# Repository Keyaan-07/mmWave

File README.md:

# mmWave Radar
This project includes building a complete mmWave radar that could operate at 60GHz. It uses the Texas Instruments IWRL6432 as the radar IC. This radar IC is operable between 57GHz-64GHz. The main goal of this project is to make a small module to use this IC as a radar. 
The board is a 6 layer board(4 layer was possible but 6 layers was cheaper). The 6 layer board costs only $2. 

[KICANVAS](https://kicanvas.org?)

# Images
Schematic:  
  
PCB:  

3d: 

# BOM
because the top sides contains BGA footprint which i've never soldered before, i am doing PCBA services for the top side and i will assemble the bottom side by myself
| ITEM                        | COST  | NOTE                           |
| --------------------------- | ----- | ------------------------------ |
| PCB                         | 2     | 6-Layer PCB                    |
| PCBA                        | 51.71 | PCBA service from jlcpcb.com   |
| SHIPPING from JLC           | 9.28  | shipping cost                  |
| PCBA discount               | -15    | 15 USD coupon from JLCONE yayy(valid till 19 sept) |
| LCSC Total (BOM_PCB_Bottom) | 14.55 | bottom side all parts          |
| Total                       | 62.54 | USD                            |

----
### BOM - Top Side of PCB(PCBA recommened)
| Designator                          | Designation      | Footprint                              | Price   | Quantity(for 2 PCBA) | Amount(USD) | JLCPCB Part Number |
| ----------------------------------- | ---------------- | -------------------------------------- | ------- | -------------------- | ----------- | ------------------ |
| C1, C2                              | 15p              | 402                                    | 0.001   | 4                    | 0.004       | C1548              |
| C6, C8, C10, C12, C14               | 2u2              | 603                                    | 0.006   | 10                   | 0.06        | C23630             |
| C5, C11, C13, C18, C19, C25, C7, C9 | 10u              | 603                                    | 0.056   | 16                   | 0.896       | C19702             |
| R2, R3                              | 100k             | 402                                    | 0.001   | 2                    | 0.002       | C25741             |
| R4, R5, R6                          | 10k              | 402                                    | 0.001   | 3                    | 0.003       | C25744             |
| U1                                  | IWRL6432BDBAAMFR | BGA-102_L6.5-W6.5-P0.50-TL_TI_IWRL6432 | 16.0095 | 2                    | 32.019      | C22428198          |
| U2                                  | W25Q128JVS       | SOIC-8_5.3x5.3mm_P1.27mm               | 1.131   | 2                    | 2.262       | C97521             |
| U3                                  | AMS1117-3.3      | SOT-223-3_TabPin2                      | 0.1615  | 2                    | 0.323       | C6186              |
|                                     |                  |                                        |         | Total                | 35.569      |                    |
| PCB Cost                            | 2                | USD                                    |         |                      |             |                    |
| Economic PCBA price                 | 51.71            | USD                                    |         |                      |             |                    |
| Total                               | 53.71            | USD                                    |         |                      |             |                    |

----
### BOM - bottom side of PCB(order and solder yourself)
if DNO is yes, i am not ordering the respective parts and cost has not been added to BOM.
| Designator             | Designation        | Footprint                          | DNO - Do not order | MOQ | Price  | Quantity | Amount(USD) | Supplier link                                      |
| ---------------------- | ------------------ | ---------------------------------- | ------------------ | --- | ------ | -------- | ----------- | -------------------------------------------------- |
| C3, C20, C22, C23, C24 | 10u                | 603                                | No                 | Yes | 0.0197 | 20       | 0.394       | https://www.lcsc.com/product-detail/C7393892.html  |
| C4, C21                | 2u2                | 603                                | No                 | Yes | 0.0228 | 20       | 0.456       | https://www.lcsc.com/product-detail/C48579298.html |
| C15                    | 47n                | 402                                | Yes                | \-  | 0      | 1        | 0           | https://www.lcsc.com/product-detail/C5142571.html  |
| C16, C17               | 1u                 | 603                                | No                 | Yes | 0.0056 | 50       | 0.28        | https://www.lcsc.com/product-detail/C29936.html    |
| L1                     | 470n               | 805                                | No                 | Yes | 0.098  | 5        | 0.49        | https://www.lcsc.com/product-detail/C45385171.html |
| L2                     | 100n               | 805                                | No                 | Yes | 0.098  | 5        | 0.49        | https://www.lcsc.com/product-detail/C45385168.html |
| R1                     | 10k                | 402                                | Yes                | \-  | 0      | 1        | 0           | https://www.lcsc.com/product-detail/C3020235.html  |
| R7                     | 100k               | 402                                | No                 | Yes | 0.0277 | 20       | 0.554       | https://www.lcsc.com/product-detail/C313329.html   |
| R8                     | 18k                | 402                                | No                 | Yes | 0.005  | 10       | 0.05        | https://www.lcsc.com/product-detail/C2759512.html  |
| U4                     | TPS628502QDRLRQ1   | SOT-583-8_L2.1-W1.2-P0.50-LS1.6-BR | No                 | No  | 1.94   | 3        | 5.82        | https://www.lcsc.com/product-detail/C3193229.html  |
| Y1                     | 40MHz Crystal      | Crystal_SMD_3225-4Pin_3.2x2.5mm    | No                 | Yes | 5      | 0.1679   | 0.8395      | https://www.lcsc.com/product-detail/C18221410.html |
| J1                     | Connector_02x08    | connector_pin2.54mm                | No                 | Yes | 5      | 0.0586   | 0.293       | https://www.lcsc.com/product-detail/C42431811.html |
|                        |                    |                                    |                    |     |        |          |             |                                                    |
|                        | Merchandise total: | 7.88                               | USD                |     |        |          |             |                                                    |
|                        | Shipping           | 3.77                               | USD                |     |        |          |             |                                                    |
|                        | Handling charges   | 3                                  | USD                |     |        |          |             |                                                    |
|                        | Discount           | \-0.1                              | USD                |     |        |          |             |                                                    |
|                        | Total              | 14.55                              | USD                |     |        |          |             |                                                    |

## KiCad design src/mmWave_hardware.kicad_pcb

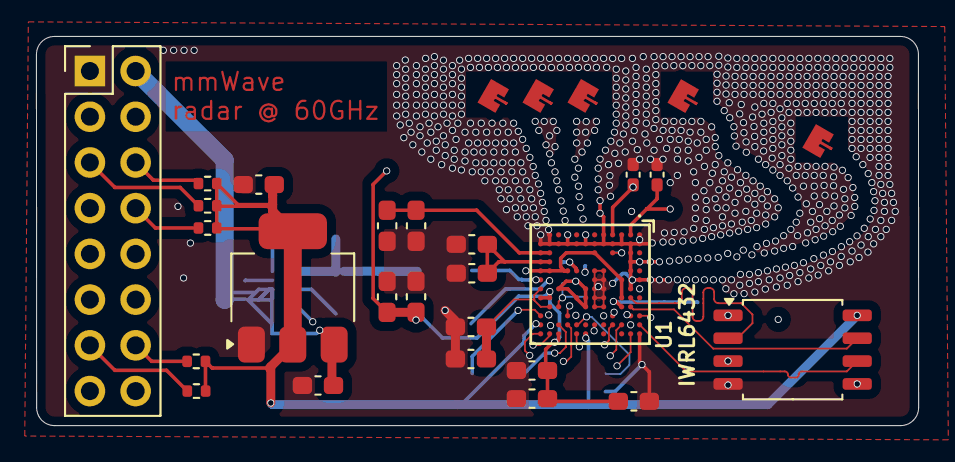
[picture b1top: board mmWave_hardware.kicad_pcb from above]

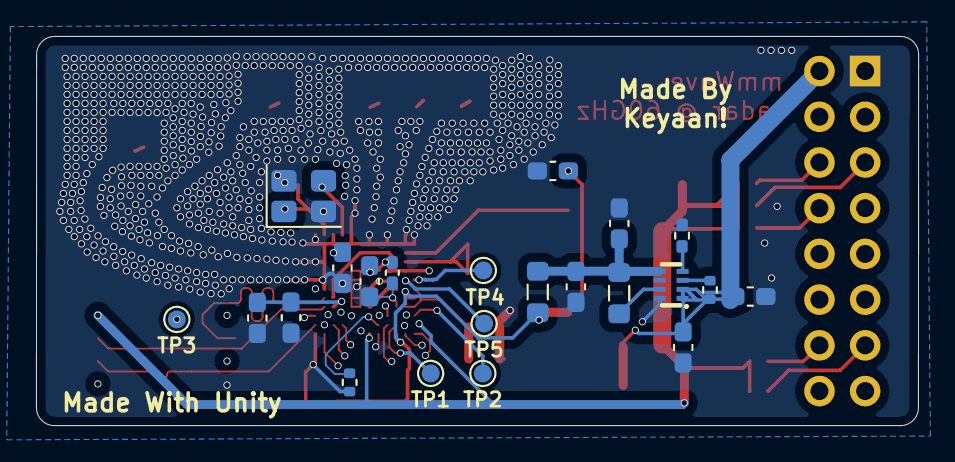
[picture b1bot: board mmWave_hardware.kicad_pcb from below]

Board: 6 copper layers, 49.0 x 21.6 mm, 48 parts (22 on the bottom side), 46 nets.

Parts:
AE1: Antenna; TX_60GHz_microstrip_inset_patch
AE2: Antenna; RX_60GHz_microstrip_inset_patch
C1, C2: 15p; C_0402_1005Metric_Pad0.74x0.62mm_HandSolder
C3, C5, C7, C9, C11, C13, C18, C19, C20, C22, C23, C24, C25: 10u; C_0603_1608Metric_Pad1.08x0.95mm_HandSolder
C4, C6, C8, C10, C12, C14, C21: 2u2; C_0603_1608Metric_Pad1.08x0.95mm_HandSolder
C15: 47n; C_0402_1005Metric_Pad0.74x0.62mm_HandSolder
C16, C17: 1u; C_0603_1608Metric_Pad1.08x0.95mm_HandSolder
J1: Conn_02x08_Top_Bottom; PinHeader_2x08_P2.54mm_Vertical
L1: 470n; L_0805_2012Metric_Pad1.05x1.20mm_HandSolder
L2: 100n; L_0805_2012Metric_Pad1.05x1.20mm_HandSolder
R1, R4, R5, R6: 10k; R_0402_1005Metric
R2, R3, R7: 100k; R_0402_1005Metric
R8: 18k; R_0402_1005Metric_Pad0.72x0.64mm_HandSolder
TP1, TP2, TP3, TP4, TP5: TestPoint; TestPoint_Pad_D1.0mm
U1: IWRL6432BDBAAMFR; BGA-102_L6.5-W6.5-P0.50-TL_TI_IWRL6432BDQGAMFR
U2: W25Q128JVS; SOIC-8_5.3x5.3mm_P1.27mm
U3: AMS1117-3.3; SOT-223-3_TabPin2
U4: TPS628502QDRLRQ1; SOT-583-8_L2.1-W1.2-P0.50-LS1.6-BR
Y1: 40.000; Crystal_SMD_3225-4Pin_3.2x2.5mm

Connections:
1v2: C3.1, C4.1, U1.C9 (VDD), U1.G7 (VDD), U1.G8 (VDD), U1.G9 (VDD), U1.H8 (VDD), U1.K7 (VDD)
1v8: C9.1, C10.1, C13.1, C14.1, C23.1, C25.1, L2.2, U1.C6 (VIOIN_I8CLK), U1.C8 (VIOIN_18), U1.F3 (VDDA_18VCO), U1.J5 (VIN_18PM), U1.K12 (VIOIN_18), U1.L5 (VDDA_18BB), U1.L8 (VIOIN_18), U1.M5 (VDDA_18BB), U1.M8 (VIOIN_18)
3v3: C19.1, R2.2, R3.1, R4.2, R5.2, R6.2, U1.G12 (VIOIN), U1.M11 (VIOIN), U2.8 (VCC), U3.2 (VO)
/CLKM: C2.2, U1.B1 (CLKM), Y1.1
/CLKP: C1.2, U1.D1 (CLKP), Y1.3
/QSPI_0: U1.B11 (QSPI[0]), U2.5 (DI/IO_{0})
/QSPI_1: U1.B8 (QSPI[1]), U2.2 (DO/IO_{1})
/QSPI_2: U1.B10 (QSPI[2]), U2.3 (~WP/IO_{2})
/QSPI_3: U1.B9 (QSPI[3]), U2.7 (~HOLD/~RESET/IO_{3})
/QSPI_CLK: U1.A11 (QSPI_CLK), U2.6 (CLK)
/QSPI_CS: U1.A10 (QSPI_CS), U2.1 (~CS)
GND: C1.1, C2.1, C3.2, C4.2, C5.1, C6.1, C7.2, C8.2, C9.2, C10.2, C11.1, C12.1, C13.2, C14.2, C15.1, C16.1, C17.1, C18.2, C19.2, C20.2, C21.2, C22.2, C23.2, C24.2, C25.2, J1.1, R1.1, R8.2, U1.A1 (VSSA), U1.A2 (VSSA), U1.A4 (VSSA), U1.A6 (VSSA), U1.A12 (VSS), U1.B2 (VSSA), U1.B3 (VSSA), U1.B4 (VSSA), U1.B5 (VSSA), U1.B6 (VSSA), U1.B7 (VSS), U1.C1 (VSSA), U1.C2 (VSSA), U1.D2 (VSSA), U1.E1 (VSSA), U1.E2 (VSSA), U1.E5 (VSSA_PM), U1.E6 (VSS), U1.E7 (VSS), U1.E8 (VSS), U1.E9 (VSS), U1.F2 (VSSA), U1.F5 (VSSA), U1.F6 (VSS), U1.F7 (VSS), U1.F8 (VSS), U1.F9 (VSS), U1.G1 (VSSA), U1.G2 (VSSA), U1.H2 (VSSA), U1.H12 (VSS), U1.J1 (VSSA), U1.J2 (VSSA), U1.K2 (VSSA), U1.K9 (VSS), U1.L1 (VSSA), U1.L2 (VSSA), U1.M1 (VSSA), U1.M2 (VSSA), U1.M12 (VSS), U2.4 (GND), U3.1 (GND), U4.8 (GND), Y1.2, Y1.4
GPIO_2: J1.3, U1.H10 (GPIO_2)
GPIO_5: J1.4, U1.J10 (GPIO_5)
NRST_MAIN: J1.8, R6.1, U1.L10 (NRESET)
unnamed: C5.2, C6.2, U1.L3 (VDDA_10RF), U1.M3 (VDDA_10RF)
unnamed: C7.1, C8.1, U1.L4 (VDDA_12RF), U1.M4 (VDDA_12RF)
unnamed: TP4.1, U1.M6 (GPADC1)
unnamed: TP5.1, U1.L6 (GPADC2)
unnamed: TP2.1, U1.M10 (HOST_CLK_REQ)
unnamed: TP1.1, U1.K11 (NERROR_OUT)
unnamed: TP3.1, U1.A7 (OSC_CLK_OUT)
unnamed: R1.2, U1.H11 (PMIC_CLKOUT)
unnamed: AE2.1 (A), U1.K1 (RX1)
unnamed: AE2.2 (A), U1.H1 (RX2)
unnamed: AE2.3 (A), U1.F1 (RX3)
unnamed: AE1.1 (A), U1.A3 (TX1)
unnamed: AE1.2 (A), U1.A5 (TX2)
unnamed: C15.2, U1.H5 (VBGAP)
unnamed: C16.2, U1.G5 (VOUT_14APLL)
unnamed: C17.2, U1.D3 (VOUT_14SYNTH)
unnamed: R8.1, U4.4 (COMP/FSET)
unnamed: C22.1, C24.1, L1.2, L2.1, U4.5 (FB)
unnamed: R7.2, U4.3 (MODE/SYNC)
unnamed: L1.1, U4.7 (SW)
RS232_RX: J1.5, R2.1, U1.F11 (RS232_RX)
RS232_TX: J1.6, R3.2, U1.E10 (RS232_TX)
SPI0_CLK: J1.14, R4.1, U1.D10 (SPIA_CLK)
SPI0_CS0_N: J1.13, R5.1, U1.D11 (SPIA_CS0_N)
SPI0_MISO: J1.16, U1.C11 (SPIA_MISO)
SPI0_MOSI: J1.15, U1.B12 (SPIA_MOSI)
UART_RTS: J1.10, U1.L11 (UARTA_RTS)
UART_RX: J1.11, U1.J11 (UARTA_RX)
UART_TX: J1.12, U1.L12 (UARTA_TX)
VDD_SRAM: C11.2, C12.2, U1.L9 (VNWA), U1.M7 (VDD_SRAM)
VIN: C18.1, C20.1, C21.1, J1.2, R7.1, U3.3 (VI), U4.1 (VIN), U4.2 (EN)

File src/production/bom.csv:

Designator,Footprint,Quantity,Value,LCSC Part #
AE1,TX_60GHz_microstrip_inset_patch,1,Antenna,
AE2,RX_60GHz_microstrip_inset_patch,1,Antenna,
"C1, C2",0402,2,15p,
"C10, C12, C14, C21, C4, C6, C8",0603,7,2u2,
"C11, C13, C18, C19, C20, C22, C23, C24, C25, C3, C5, C7, C9",0603,13,10u,
C15,0402,1,47n,
"C16, C17",0603,2,1u,
J1,PinHeader_2x08_P2.54mm_Vertical,1,Conn_02x08_Top_Bottom,
L1,0805,1,470n,
L2,0805,1,100n,
"R1, R4, R5, R6",0402,4,10k,
"R2, R3, R7",0402,3,100k,
R8,0402,1,18k,
"TP1, TP2, TP3, TP4, TP5",TestPoint_Pad_D1.0mm,5,TestPoint,
U1,BGA-102_L6.5-W6.5-P0.50-TL_TI_IWRL6432BDQGAMFR,1,IWRL6432BDBAAMFR,C22428198
U2,SOIC-8_5.3x5.3mm_P1.27mm,1,W25Q128JVS,
U3,SOT-223-3_TabPin2,1,AMS1117-3.3,
U4,SOT-583-8_L2.1-W1.2-P0.50-LS1.6-BR,1,TPS628502QDRLRQ1,C3193229
Y1,Crystal_SMD_3225-4Pin_3.2x2.5mm,1,40.000,

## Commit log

2025-08-10 journaling
2025-08-20 images added
2025-08-20 schematic
2025-08-22 images
2025-08-22 sch+pcb
2025-08-23 new buck conv
2025-08-25 layout
2025-08-25 added images
2025-08-25 antennaaaaaaaaaaaaaaaaaaaaa
2025-08-26 antenna array
2025-08-26 antennas(RX+TX)
2025-08-26 layout image upload
2025-08-26 Layout Complete
2025-08-28 added images of pcb
2025-08-28 PCB Complete
2025-08-30 PCB Done
2025-08-30 images of final pcb
2025-08-31 backups
2025-08-31 pcb changes
2025-09-02 unrouting started
2025-09-04 unrouted all
2025-09-06 routing done
2025-09-06 added README.md
2025-09-06 Final PCB(Probably)
2025-09-10 updated production files
2025-09-10 fixed footprint issue
2025-09-10 changed silkscreen
2025-09-11 added PCB images
2025-09-11 Update Images in README
2025-09-11 silkscreen changes
2025-09-17 added BOM
2025-09-17 Uploaded schematic
2025-09-17 add 3d model
2025-09-17 cart screenshot
2025-09-17 uploaded images
2025-09-17 src uploaded
2025-09-17 BOM files
2025-09-17 renamed 3d file
2025-09-17 added gerber
